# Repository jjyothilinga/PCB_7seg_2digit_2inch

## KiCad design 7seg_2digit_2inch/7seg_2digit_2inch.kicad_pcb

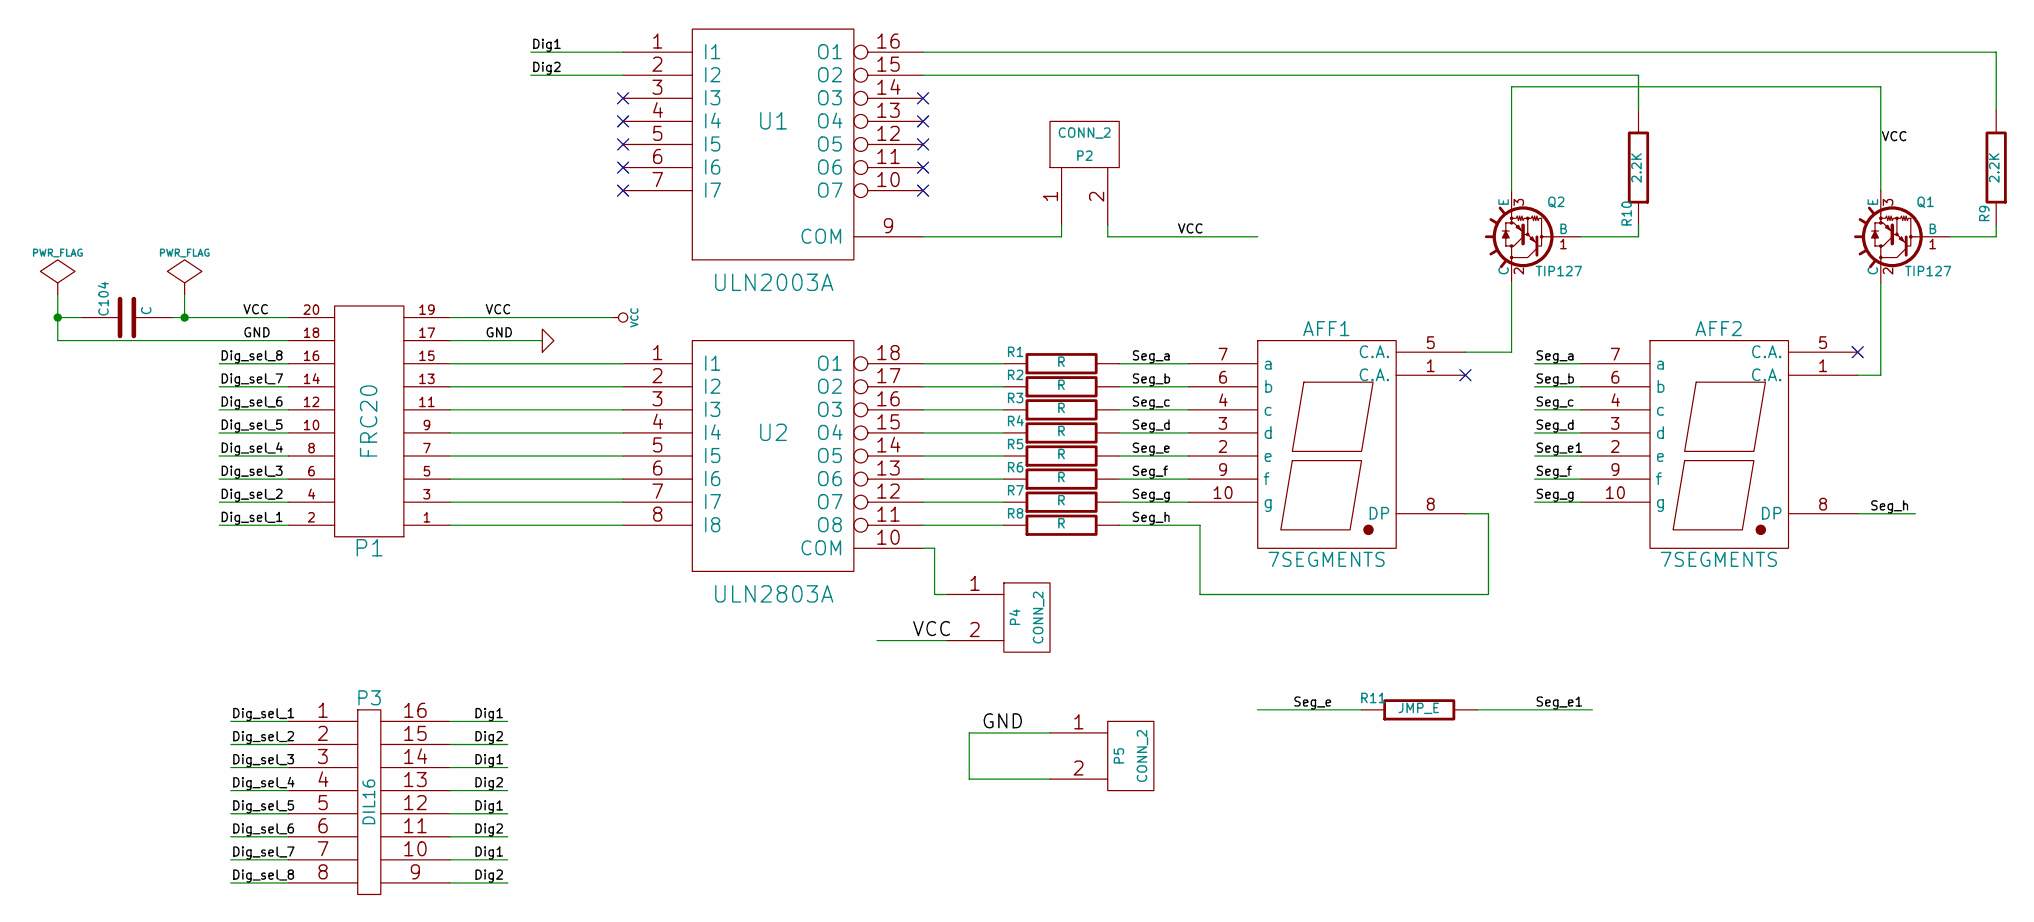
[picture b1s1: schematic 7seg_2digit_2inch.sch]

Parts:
AFF1, AFF2: 7SEGMENTS
C104: C
P1: FRC20
P2, P4, P5: CONN_2
P3: DIL16
Q1, Q2: TIP127; TO220
R1, R2, R3, R4, R5, R6, R7, R8: R
R9, R10: 2.2K
R11: JMP_E
U1: ULN2003A
U2: ULN2803A

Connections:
/Dig1: P3.10, P3.12, P3.14, P3.16, U1.1 (I1)
/Dig2: P3.9, P3.11, P3.13, P3.15, U1.2 (I2)
/Dig_sel_1: P1.2, P3.1
/Dig_sel_2: P1.4, P3.2
/Dig_sel_3: P1.6, P3.3
/Dig_sel_4: P1.8, P3.4
/Dig_sel_5: P1.10, P3.5
/Dig_sel_6: P1.12, P3.6
/Dig_sel_7: P1.14, P3.7
/Dig_sel_8: P1.16, P3.8
/Seg_a: AFF1.7 (a), AFF2.7 (a), R1.2
/Seg_b: AFF1.6 (b), AFF2.6 (b), R2.2
/Seg_c: AFF1.4 (c), AFF2.4 (c), R3.2
/Seg_d: AFF1.3 (d), AFF2.3 (d), R4.2
/Seg_e: AFF1.2 (e), R5.2, R11.1
/Seg_e1: AFF2.2 (e), R11.2
/Seg_f: AFF1.9 (f), AFF2.9 (f), R6.2
/Seg_g: AFF1.10 (g), AFF2.10 (g), R7.2
/Seg_h: AFF1.8 (DP), AFF2.8 (DP), R8.2
GND: C104.1, P1.17, P1.18, P5.1, P5.2 (PM), U1.8 (GND), U2.9 (GND); also elsewhere on the board
unnamed: P1.7, U2.5 (I5)
unnamed: P1.15, U2.1 (I1)
unnamed: P1.13, U2.2 (I2)
unnamed: P1.11, U2.3 (I3)
unnamed: P1.9, U2.4 (I4)
unnamed: P1.5, U2.6 (I6)
unnamed: P1.3, U2.7 (I7)
unnamed: P1.1, U2.8 (I8)
unnamed: AFF2.1 (C.A.), Q1.2 (C)
unnamed: AFF1.5 (C.A.), Q2.2 (C)
unnamed: R9.2, U1.16 (O1)
unnamed: R10.2, U1.15 (O2)
unnamed: R8.1, U2.11 (O8)
unnamed: P4.1, U2.10 (COM)
unnamed: R1.1, U2.18 (O1)
unnamed: R2.1, U2.17 (O2)
unnamed: R3.1, U2.16 (O3)
unnamed: R4.1, U2.15 (O4)
unnamed: R5.1, U2.14 (O5)
unnamed: R6.1, U2.13 (O6)
unnamed: R7.1, U2.12 (O7)
unnamed: P2.1, U1.9 (COM)
unnamed: Q1.1 (B), R9.1
unnamed: Q2.1 (B), R10.1
VCC: C104.2, P1.19, P1.20, P2.2 (PM), P4.2 (PM), Q1.3 (E), Q2.3 (E)

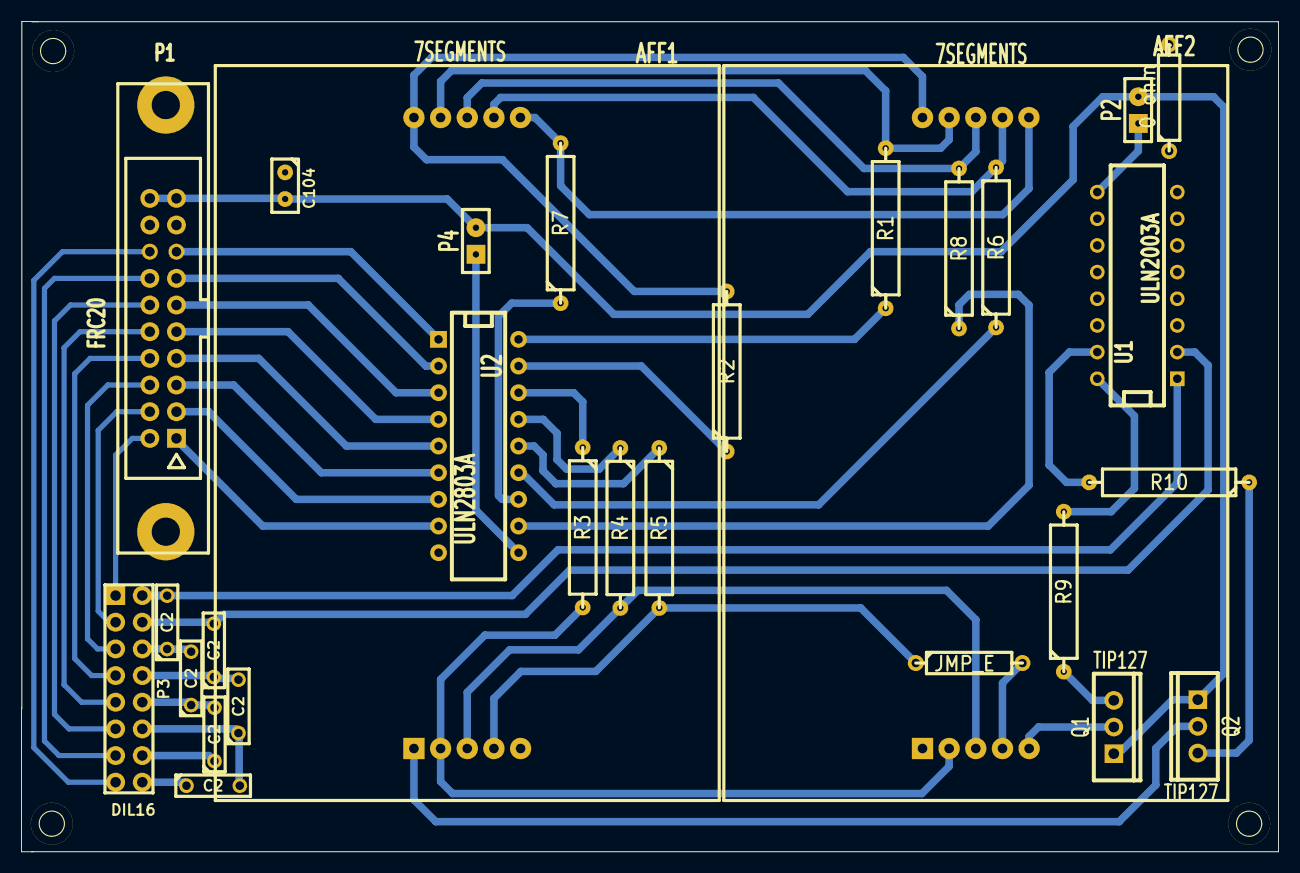
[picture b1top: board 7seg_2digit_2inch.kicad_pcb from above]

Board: 2 copper layers, 119.7 x 79.1 mm, 29 parts (0 on the bottom side), 45 nets.

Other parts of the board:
0 ohm: CONN_2; R4
C2, C2#2, C2#3, C2#4, C2#5, C2#6: C***; C2

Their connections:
GND: 0 ohm.1, 0 ohm.2; also elsewhere on the board

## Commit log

2015-05-30 :tada: Added .gitattributes & .gitignore files
2015-05-30 Project creation
